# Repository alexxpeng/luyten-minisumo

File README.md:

# luyten-minisumo
500g Autonomous/RC Mini Robot Sumo

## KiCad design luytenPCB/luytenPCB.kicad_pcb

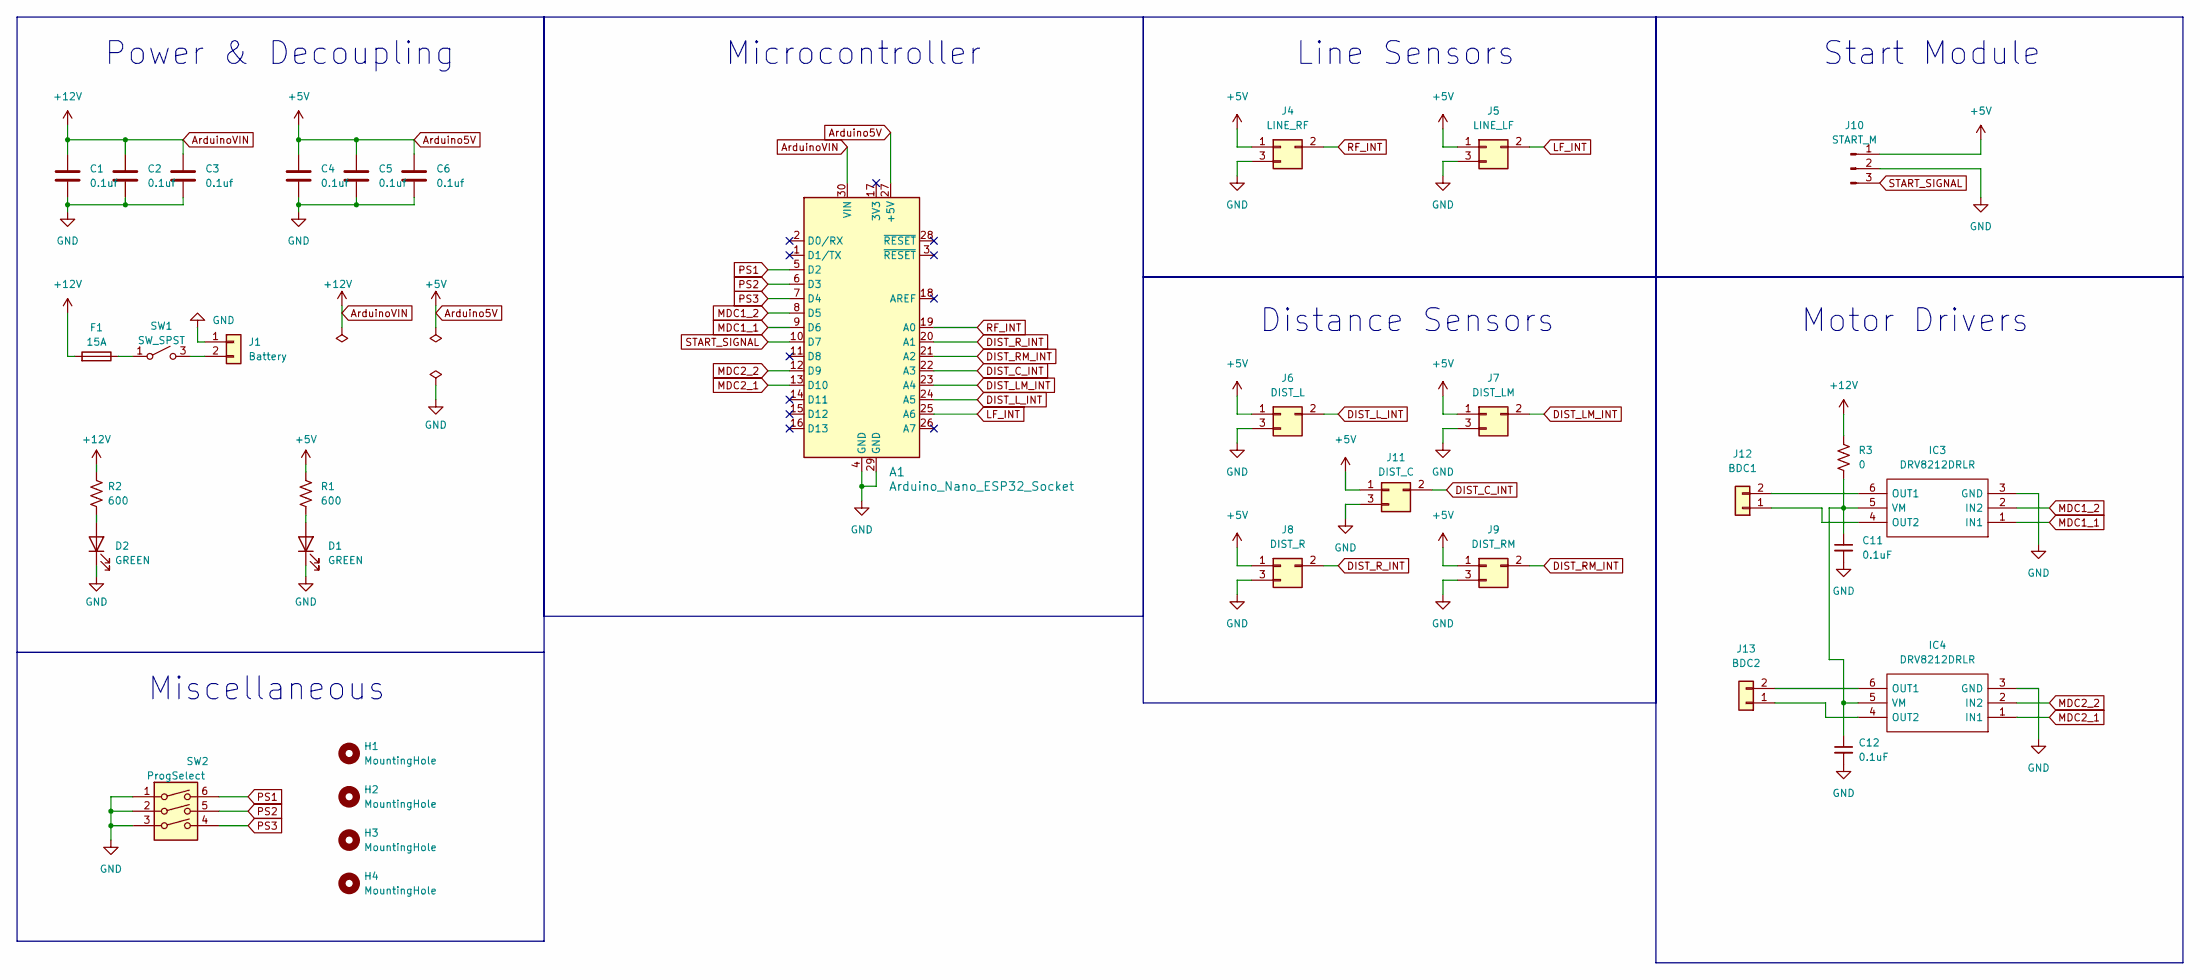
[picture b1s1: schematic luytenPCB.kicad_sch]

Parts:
A1: Arduino_Nano_ESP32_Socket; Arduino_Nano
C1, C2, C3, C4, C5, C6: 0.1uf; C_0805_2012Metric_Pad1.18x1.45mm_HandSolder
C11, C12: 0.1uF; C_0805_2012Metric_Pad1.18x1.45mm_HandSolder
D1, D2: GREEN; C_0603_1608Metric_Pad1.08x0.95mm_HandSolder
F1: 15A; Fuse_1206_3216Metric_Pad1.42x1.75mm_HandSolder
H1, H2, H3, H4: MountingHole; MountingHole_2.2mm_M2_ISO7380
IC3, IC4: DRV8212DRLR; SOT-563; Manufacturer_Part_Number DRV8212DRLR; Mouser Part Number 595-DRV8212DRLR
J1: Battery; AMASS_XT30U-M_1x02_P5.0mm_Vertical
J4: LINE_RF; PinHeader_1x03_P2.54mm_Vertical
J5: LINE_LF; PinHeader_1x03_P2.54mm_Vertical
J6: DIST_L; PinHeader_1x03_P2.54mm_Vertical
J7: DIST_LM; PinHeader_1x03_P2.54mm_Vertical
J8: DIST_R; PinHeader_1x03_P2.54mm_Vertical
J9: DIST_RM; PinHeader_1x03_P2.54mm_Vertical
J10: START_M; PinSocket_1x03_P2.54mm_Vertical
J11: DIST_C; PinHeader_1x03_P2.54mm_Vertical
J12: BDC1; PinHeader_1x02_P2.54mm_Vertical
J13: BDC2; PinHeader_1x02_P2.54mm_Vertical
R1, R2: 600; D_0805_2012Metric_Pad1.15x1.40mm_HandSolder
R3: 0; PinHeader_1x02_P2.00mm_Vertical
SW1: SW_SPST; SW_AS11CP
SW2: ProgSelect; SW_DIP_SPSTx03_Slide_9.78x9.8mm_W8.61mm_P2.54mm

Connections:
Arduino5V: A1.27 (+5V), C4.1, C5.1, C6.1, J4.1, J5.1, J6.1, J7.1, J8.1, J9.1, J10.1, J11.1, R1.1
ArduinoVIN: A1.30 (VIN), C1.1, C2.1, C3.1, F1.2, R2.1, R3.1
DIST_C_INT: A1.22 (A3), J11.2
DIST_LM_INT: A1.23 (A4), J7.2
DIST_L_INT: A1.24 (A5), J6.2
DIST_RM_INT: A1.21 (A2), J9.2
DIST_R_INT: A1.20 (A1), J8.2
GND: A1.4 (GND), A1.29 (GND), C1.2, C2.2, C3.2, C4.2, C5.2, C6.2, C11.2, C12.2, D1.1 (K), D2.1 (K), IC3.3 (GND), IC4.3 (GND), J1.1, J4.3, J5.3, J6.3, J7.3, J8.3, J9.3, J10.2, J11.3, SW2.1, SW2.2, SW2.3
LF_INT: A1.25 (A6), J5.2
MDC1_1: A1.9 (D6), IC3.1 (IN1)
MDC1_2: A1.8 (D5), IC3.2 (IN2)
MDC2_1: A1.13 (D10), IC4.1 (IN1)
MDC2_2: A1.12 (D9), IC4.2 (IN2)
unnamed: D1.2 (A), R1.2
unnamed: D2.2 (A), R2.2
unnamed: IC3.6 (OUT1), J12.2
unnamed: IC3.4 (OUT2), J12.1
unnamed: C11.1, C12.1, IC3.5 (VM), IC4.5 (VM), R3.2
unnamed: IC4.6 (OUT1), J13.2
unnamed: IC4.4 (OUT2), J13.1
unnamed: J1.2, SW1.3 (B)
unnamed: F1.1, SW1.1 (A)
PS1: A1.5 (D2), SW2.6
PS2: A1.6 (D3), SW2.5
PS3: A1.7 (D4), SW2.4
RF_INT: A1.19 (A0), J4.2
START_SIGNAL: A1.10 (D7), J10.3

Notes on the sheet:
Microcontroller
Line Sensors
Distance Sensors
Motor Drivers
Start Module
Miscellaneous
Power & Decoupling

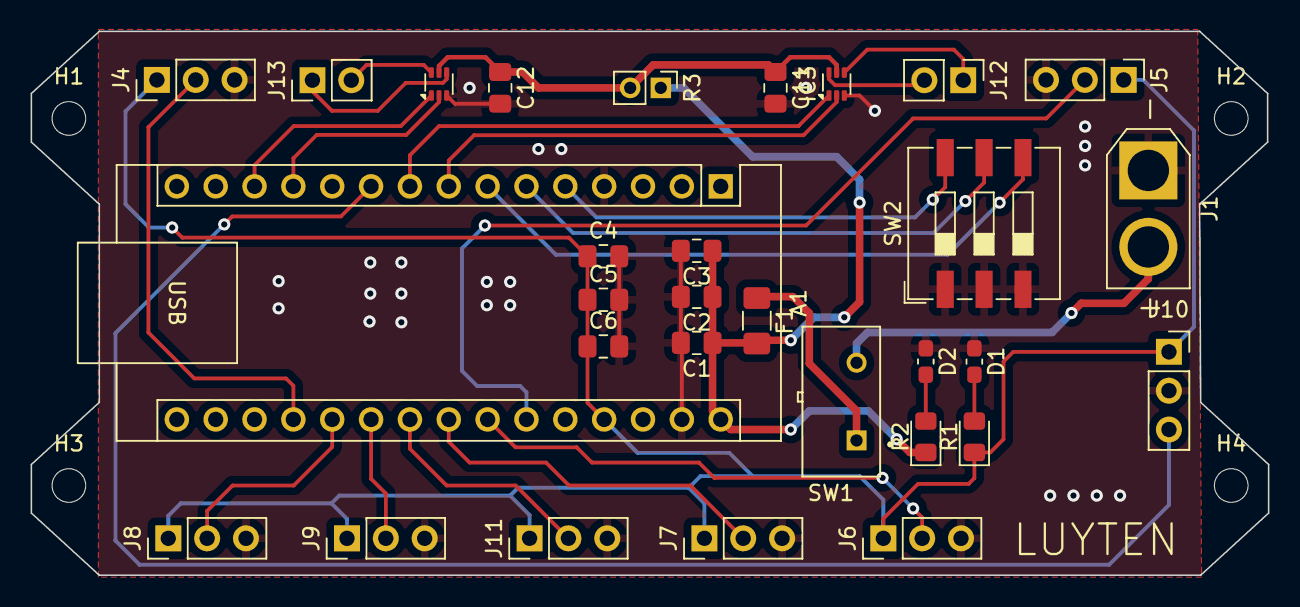
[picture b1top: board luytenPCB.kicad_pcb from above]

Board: 2 copper layers, 80.9 x 35.6 mm, 34 parts (0 on the bottom side), 27 nets.

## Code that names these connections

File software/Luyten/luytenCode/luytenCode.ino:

#define LMOTOR1 5
#define LMOTOR2 6
#define RMOTOR1 9
#define RMOTOR2 10
// Start module
#define START 7
// Distance sensors
#define LDIST A4
#define LMDIST A5
#define MDIST A3
#define RMDIST A2
#define RDIST A1
// Line sensors
#define LLS A0
#define RLS A6
// Program select
#define PS1 2
#define PS2 3
#define PS3 4

int lineThreshold = 35;  // Tunable threshold value for line sensors, 40

void setup() {
  // Set motor pins as output
  pinMode(LMOTOR1, OUTPUT);
  pinMode(LMOTOR2, OUTPUT);
  pinMode(RMOTOR1, OUTPUT);
  pinMode(RMOTOR2, OUTPUT);

  // Set sensor pins as input
  pinMode(LDIST, INPUT);
  pinMode(LMDIST, INPUT);
  pinMode(MDIST, INPUT);
  pinMode(RMDIST, INPUT);
  pinMode(RDIST, INPUT);
  pinMode(LLS, INPUT);
  pinMode(RLS, INPUT);
  pinMode(START, INPUT);
  pinMode(PS1, INPUT_PULLUP);
  pinMode(PS2, INPUT_PULLUP);
  pinMode(PS3, INPUT_PULLUP);

  // Initialize serial communication for debug mode
  if (debugMode) {
    Serial.begin(9600);
  }

  // Start with motors off
  stopMotors();
}

void loop() {
  // Read sensor values
  bool leftDist = digitalRead(LDIST);
  bool leftMidDist = digitalRead(LMDIST);
  bool midDist = digitalRead(MDIST);
  bool rightMidDist = digitalRead(RMDIST);
  bool rightDist = digitalRead(RDIST);
  int leftLine = analogRead(LLS);
  int rightLine = analogRead(RLS);
  int progSel = readProgramSelection();

  if (digitalRead(START) == HIGH) {
    switch (progSel) {
      case 0:
        debugMode(leftDist, leftMidDist, midDist, rightMidDist, rightDist, leftLine, rightLine);  // Default program: stop motors
        break;
      case 1:
        defensive(leftDist, leftMidDist, midDist, rightMidDist, rightDist, leftLine, rightLine);
        break;
      case 2:
        attack(leftDist, leftMidDist, midDist, rightMidDist, rightDist, leftLine, rightLine);
        break;
      case 3:
        //programThree();
        break;
      case 4:
        //programFour();
        break;
      case 5:
        //programFive();
        break;
      case 6:
        //programSix();
        break;
      case 7:
        //programSeven();
        break;
      default:
        stopMotors();  // Default to stopping motors if an unknown program is selected
        break;
    }
  } else {
    stopMotors();
  }
}

int readProgramSelection() {
  int ps1 = digitalRead(PS1);
  int ps2 = digitalRead(PS2);
  int ps3 = digitalRead(PS3);

  // Convert binary inputs to a single integer (0-7)
  return (ps1 << 2) | (ps2 << 1) | ps3;
}

void debugMode(bool leftDist, bool leftMidDist, bool midDist, bool rightMidDist, bool rightDist, int leftLine, int rightLine) {
  Serial.print("LDIST: ");
  Serial.print(leftDist);
  Serial.print(" LMDIST: ");
  Serial.print(leftMidDist);
  Serial.print(" MDIST: ");
  Serial.print(midDist);
  Serial.print(" RMDIST: ");
  Serial.print(rightMidDist);
  Serial.print(" RDIST: ");
  Serial.print(rightDist);
  Serial.print(" LLS: ");
  Serial.print(leftLine);
  Serial.print(" RLS: ");
  Serial.print(rightLine);
  Serial.print(" ProgSel: ");
  Serial.println(readProgramSelection());
  delay(100);  // Delay to make it readable
}

void defensive(bool leftDist, bool leftMidDist, bool midDist, bool rightMidDist, bool rightDist, int leftLine, int rightLine) {
  if (leftLine < lineThreshold) {
    moveBackward(80);
    delay(160);
    turnRightS(160);
    delay(160);
    //moveForward(40);
    //delay(100);
  } else if (rightLine < lineThreshold){
    moveBackward(80);
    delay(160);
    turnLeftS(160);
    delay(160);
    //moveForward(40);
    //delay(100);
  } else if (midDist) {
    moveForward(125);
  } else if (leftMidDist) {
    turnRight(200);
  } else if (rightMidDist) {
    turnLeft(200);
  } else if (leftDist) {
    turnRightS(200);
  } else if (rightDist) {
    turnLeftS(200);
  } else {
    stopMotors();
  }
}

int midDistCounter = 0; // Initialize a counter for midDist
void attack(bool leftDist, bool leftMidDist, bool midDist, bool rightMidDist, bool rightDist, int leftLine, int rightLine) {  
  if (leftLine < lineThreshold) {
    moveBackward(110);
    delay(180);
    turnRightS(160);
    delay(80);
    midDistCounter = 0; // Reset counter
  } 
  else if (rightLine < lineThreshold) {
    moveBackward(110);
    delay(180);
    turnLeftS(160);
    delay(80);
    midDistCounter = 0; // Reset counter
  } 
  else if (midDist) {
    midDistCounter++; // Increase counter
    moveForward(135 + (midDistCounter * 5)); // Increase speed progressively
  } 
  else if (leftMidDist) {
    turnRight(200);
    midDistCounter = 0; // Reset counter
  } 
  else if (rightMidDist) {
    turnLeft(200);
    midDistCounter = 0; // Reset counter
  } 
  else if (leftDist) {
    turnRightS(200);
    midDistCounter = 0; // Reset counter
  } 
  else if (rightDist) {
    turnLeftS(200);
    midDistCounter = 0; // Reset counter
  } 
  else {
    moveForward(45);
    midDistCounter = 0; // Reset counter
  }
}

void stopMotors() {
  analogWrite(LMOTOR1, 255);
  analogWrite(LMOTOR2, 255);
  analogWrite(RMOTOR1, 255);
  analogWrite(RMOTOR2, 255);
}

void moveForward(int motorSpeed) {
  analogWrite(LMOTOR1, motorSpeed);
  analogWrite(LMOTOR2, 0);
  analogWrite(RMOTOR1, motorSpeed);
  analogWrite(RMOTOR2, 0);
}

void moveBackward(int motorSpeed) {
  analogWrite(LMOTOR1, 0);
  analogWrite(LMOTOR2, motorSpeed);
  analogWrite(RMOTOR1, 0);
  analogWrite(RMOTOR2, motorSpeed);
}

void turnRight(int motorSpeed) {
  analogWrite(LMOTOR1, 255);
  analogWrite(LMOTOR2, 255);
  analogWrite(RMOTOR1, motorSpeed);
  analogWrite(RMOTOR2, 0);
}

void turnLeft(int motorSpeed) {
  analogWrite(LMOTOR1, motorSpeed);
  analogWrite(LMOTOR2, 0);
  analogWrite(RMOTOR1, 255);
  analogWrite(RMOTOR2, 255);
}

void turnRightS(int motorSpeed) {
  analogWrite(LMOTOR1, 0);
  analogWrite(LMOTOR2, motorSpeed);
  analogWrite(RMOTOR1, motorSpeed / 2);
  analogWrite(RMOTOR2, 0);
}

void turnLeftS(int motorSpeed) {
  analogWrite(LMOTOR1, motorSpeed / 2);
  analogWrite(LMOTOR2, 0);
  analogWrite(RMOTOR1, 0);
  analogWrite(RMOTOR2, motorSpeed);
}

bool detectLine(int leftLine, int rightLine) {
  return leftLine < lineThreshold || rightLine < lineThreshold;
}

bool detectObstacle(bool leftDist, bool leftMidDist, bool midDist, bool rightMidDist, bool rightDist) {
  return leftDist || leftMidDist || midDist || rightMidDist || rightDist;
}

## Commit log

2024-01-31 init
    schematic done
2024-02-02 pcb production prototype done
    finished schematic and layout
2024-06-02 updates
    --fixes to routing, updated screw terminal
2024-06-02 luytenv2
    forgot to update spst footprint :(
2024-08-28 revision
    changed from nano esp32 -> nano every, added dummy connection for optional kill switch circuitry, fixed switch footprint, removed leds from analog sensors
2024-09-13 i suck at software
    added working code
2024-09-28 updated motor driver drv8212
    changed some connections for compatibility with digital and analog dist sensors, updated optional kill switch circuit break
2024-10-25 added luytenCode
    0-debug
    1-defensive
    2-attack
    -todo, start strat
